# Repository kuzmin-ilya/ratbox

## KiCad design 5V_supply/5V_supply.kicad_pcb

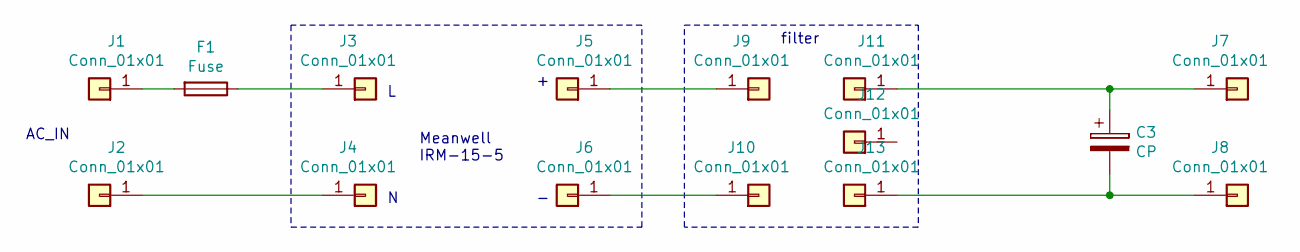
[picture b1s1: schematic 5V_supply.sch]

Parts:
C3: CP; CP_Radial_D13.0mm_P7.50mm
F1: Fuse; Fuseholder_Cylinder-5x20mm_Schurter_0031_8201_Horizontal_Op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
J1, J2, J7, J8: Conn_01x01; SolderWirePad_1x01_Drill2mm
J3, J4, J5, J6: Conn_01x01; SolderWirePad_1x01_Drill1.5mm
J9, J10, J11, J12, J13: Conn_01x01; SolderWirePad_1x01_Drill2.5mm

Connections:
unnamed: C3.1, J7.1, J11.1
unnamed: C3.2, J8.1, J13.1
unnamed: F1.1, J3.1
unnamed: F1.2, J1.1
unnamed: J2.1, J4.1
unnamed: J5.1, J9.1
unnamed: J6.1, J10.1

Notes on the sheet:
AC_IN
Meanwell IRM-15-5
filter

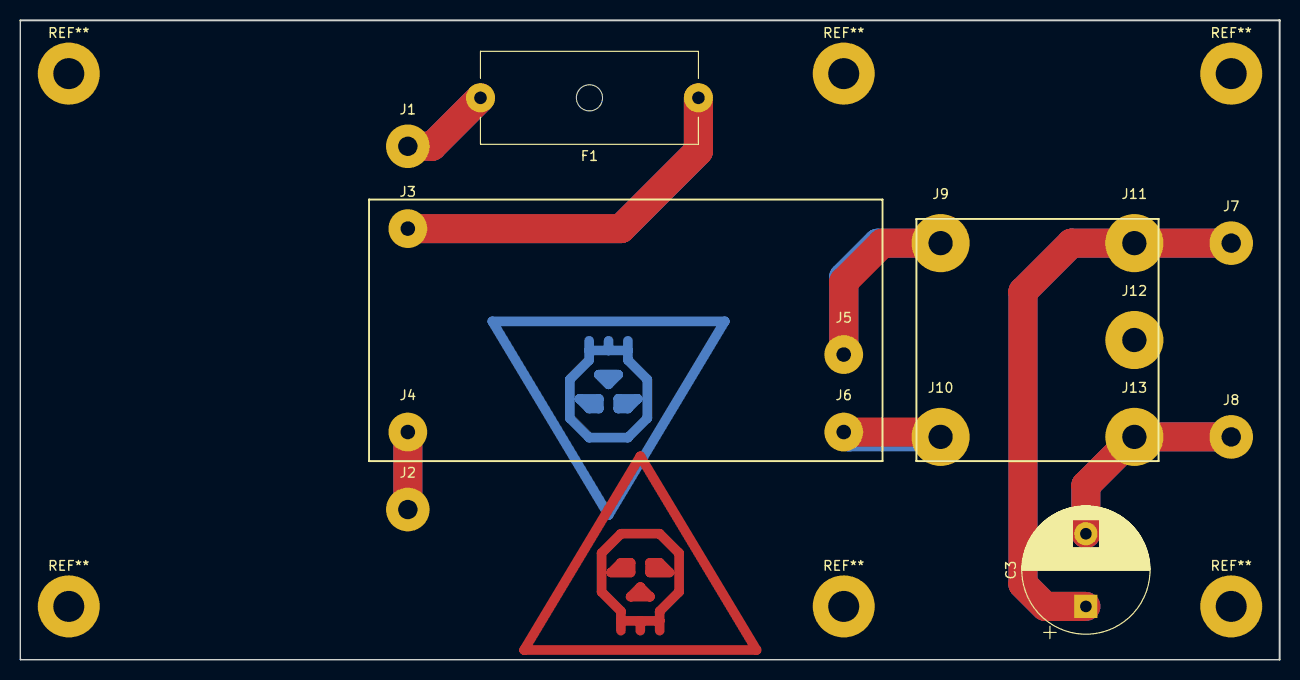
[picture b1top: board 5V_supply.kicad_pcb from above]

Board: 2 copper layers, 130.0 x 66.0 mm, 15 parts (0 on the bottom side), 7 nets.

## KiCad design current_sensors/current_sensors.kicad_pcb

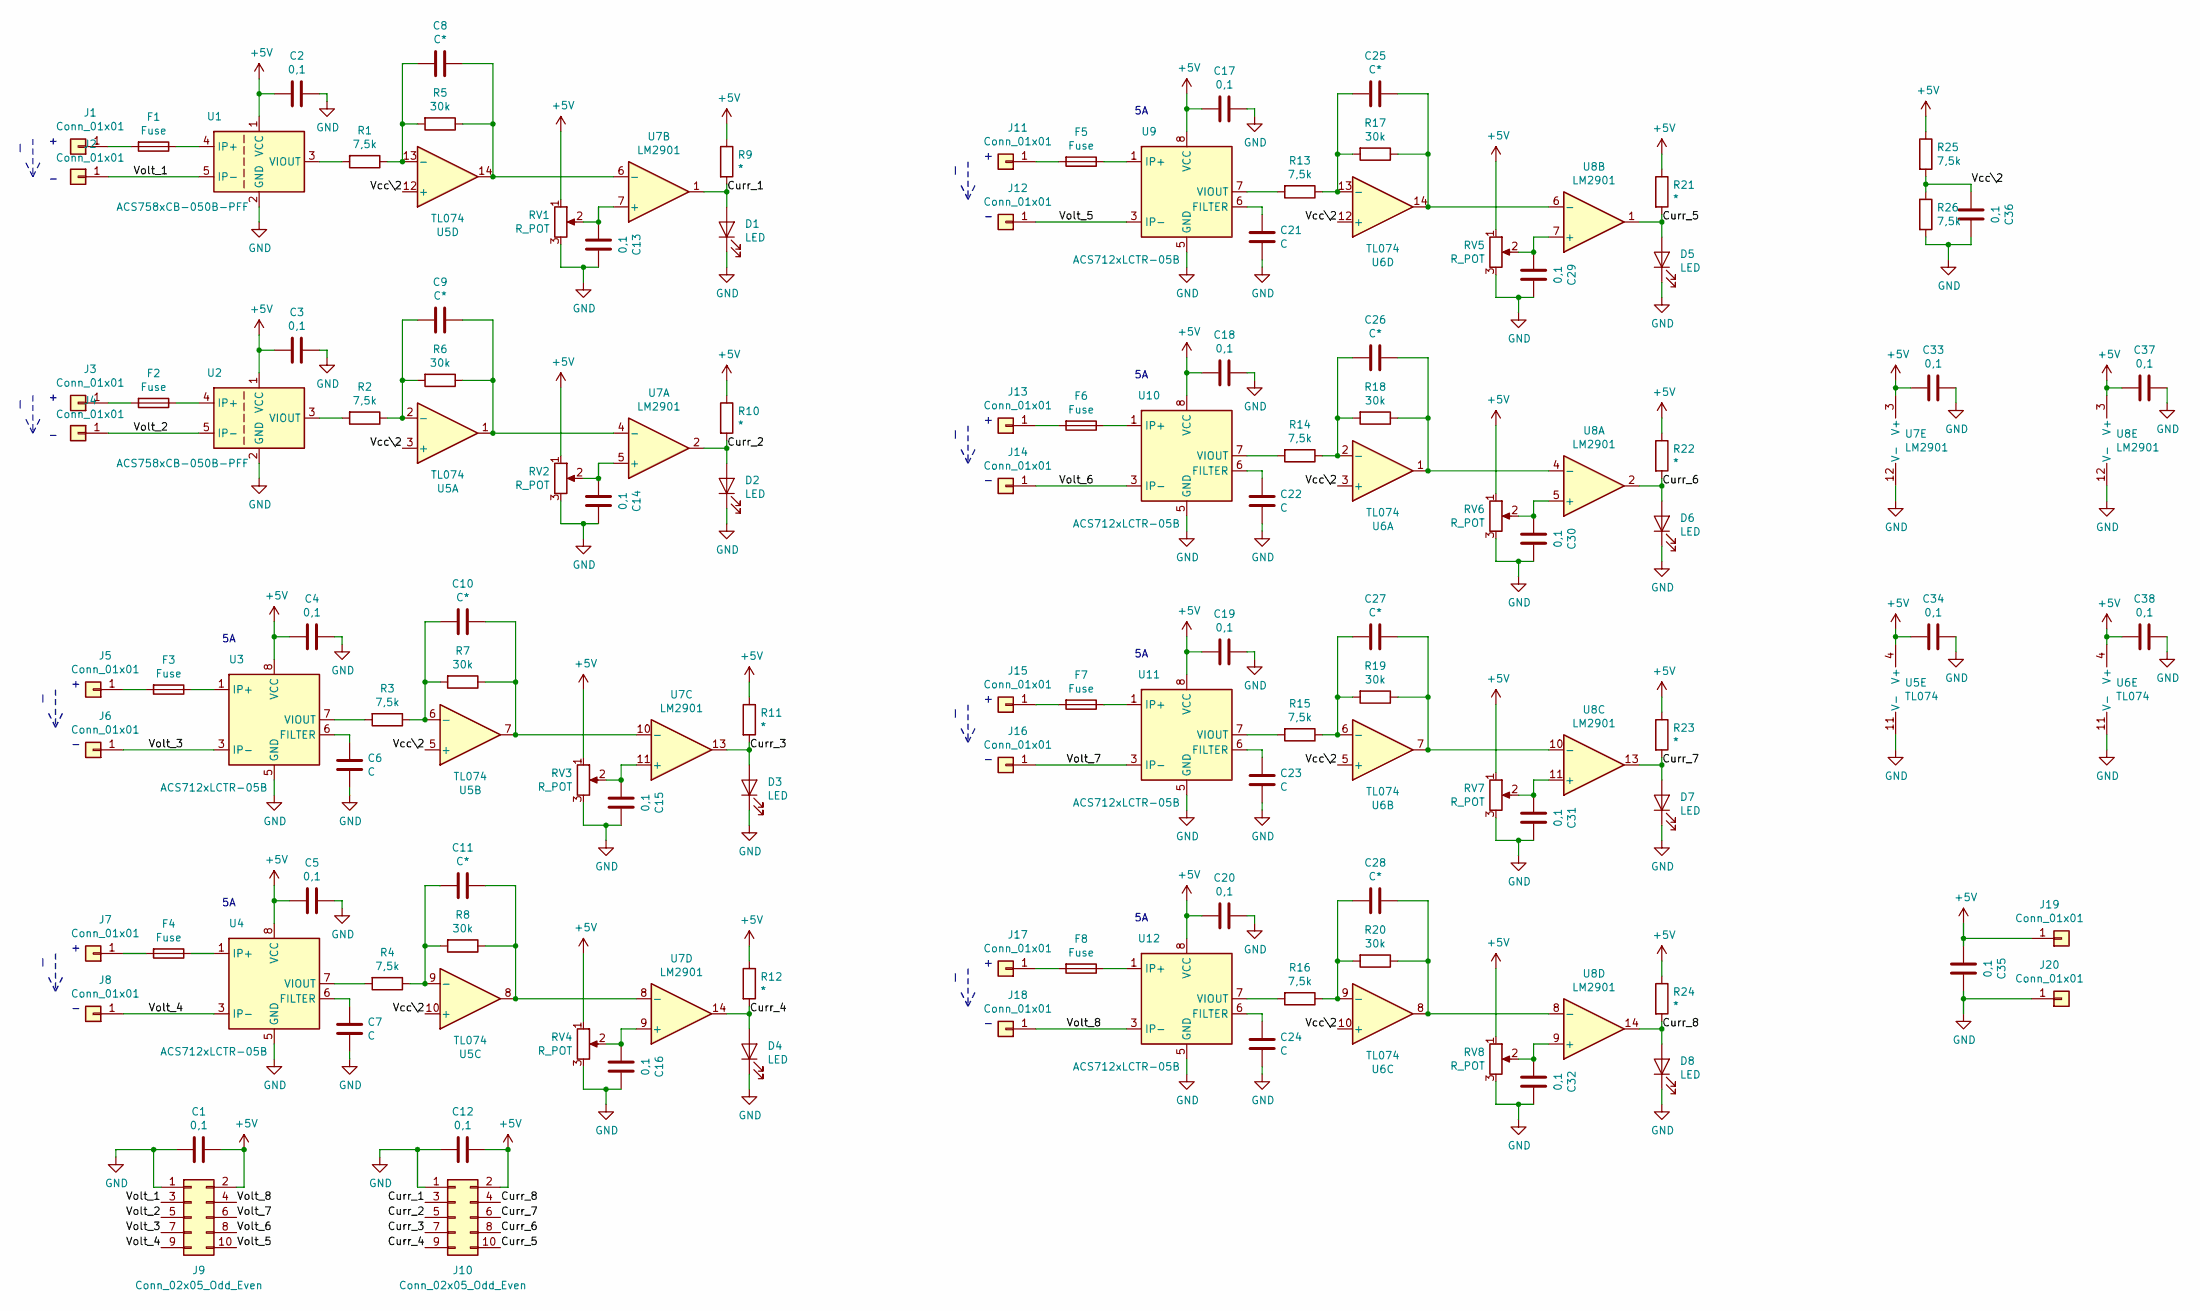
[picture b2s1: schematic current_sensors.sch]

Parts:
C1, C2, C3, C4, C5, C12, C13, C14, C15, C16, C17, C18, C19, C20, C29, C30, C31, C32, C33, C34, C35, C36, C37, C38: 0,1; C_0805_2012Metric_Pad1.15x1.40mm_HandSolder
C6, C7, C21, C22, C23, C24: C; C_0805_2012Metric_Pad1.15x1.40mm_HandSolder
C8, C9, C10, C11, C25, C26, C27, C28: C*; C_0805_2012Metric_Pad1.15x1.40mm_HandSolder
D1, D2, D3, D4, D5, D6, D7, D8: LED; LED_D5.0mm
F1, F2, F3, F4, F5, F6, F7, F8: Fuse; Fuseholder_Cylinder-5x20mm_Schurter_0031_8201_Horizontal_Op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
J1, J2, J3, J4, J5, J6, J7, J8, J11, J12, J13, J14, J15, J16, J17, J18, J19, J20: Conn_01x01; SolderWirePad_1x01_Drill2mm
J9, J10: Conn_02x05_Odd_Even; IDC-Header_2x05_P2.54mm_Vertical
R1, R2, R3, R4, R13, R14, R15, R16, R25, R26: 7,5k; R_0805_2012Metric_Pad1.15x1.40mm_HandSolder
R5, R6, R7, R8, R17, R18, R19, R20: 30k; R_0805_2012Metric_Pad1.15x1.40mm_HandSolder
R9, R10, R11, R12, R21, R22, R23, R24: *; R_0805_2012Metric_Pad1.15x1.40mm_HandSolder
RV1, RV2, RV3, RV4, RV5, RV6, RV7, RV8: R_POT; Potentiometer_Bourns_3296W_Vertical
U1, U2: ACS758xCB-050B-PFF; Allegro_CB_PFF
U3, U4, U9, U10, U11, U12: ACS712xLCTR-05B; SOIC-8_3.9x4.9mm_P1.27mm
U5, U6: TL074; SOIC-14_3.9x8.7mm_P1.27mm
U7, U8: LM2901; SOIC-14_3.9x8.7mm_P1.27mm

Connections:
+5V: C1.1, C2.2, C3.2, C4.2, C5.2, C12.1, C17.2, C18.2, C19.2, C20.2, C33.2, C34.2, C35.2, C37.2, C38.2, J9.2, J10.2, J19.1, R9.1, R10.1, R11.1, R12.1, R21.1, R22.1, R23.1, R24.1, R25.1, RV1.1, RV2.1, RV3.1, RV4.1, RV5.1, RV6.1, RV7.1, RV8.1, U1.1 (VCC), U2.1 (VCC), U3.8 (VCC), U4.8 (VCC), U5.4 (V+), U6.4 (V+), U7.3 (V+), U8.3 (V+), U9.8 (VCC), U10.8 (VCC), U11.8 (VCC), U12.8 (VCC)
/Curr_1: D1.2 (A), J10.3, R9.2, U7.1
/Curr_2: D2.2 (A), J10.5, R10.2, U7.2
/Curr_3: D3.2 (A), J10.7, R11.2, U7.13
/Curr_4: D4.2 (A), J10.9, R12.2, U7.14
/Curr_5: D5.2 (A), J10.10, R21.2, U8.1
/Curr_6: D6.2 (A), J10.8, R22.2, U8.2
/Curr_7: D7.2 (A), J10.6, R23.2, U8.13
/Curr_8: D8.2 (A), J10.4, R24.2, U8.14
/Vcc\2: C36.2, R25.2, R26.1, U5.3 (+), U5.5 (+), U5.10 (+), U5.12 (+), U6.3 (+), U6.5 (+), U6.10 (+), U6.12 (+)
/Volt_1: J2.1, J9.3, U1.5 (IP-)
/Volt_2: J4.1, J9.5, U2.5 (IP-)
/Volt_3: J6.1, J9.7, U3.3 (IP-), U3.4 (IP-)
/Volt_4: J8.1, J9.9, U4.3 (IP-), U4.4 (IP-)
/Volt_5: J9.10, J12.1, U9.3 (IP-), U9.4 (IP-)
/Volt_6: J9.8, J14.1, U10.3 (IP-), U10.4 (IP-)
/Volt_7: J9.6, J16.1, U11.3 (IP-), U11.4 (IP-)
/Volt_8: J9.4, J18.1, U12.3 (IP-), U12.4 (IP-)
GND: C1.2, C2.1, C3.1, C4.1, C5.1, C6.2, C7.2, C12.2, C13.1, C14.1, C15.1, C16.1, C17.1, C18.1, C19.1, C20.1, C21.2, C22.2, C23.2, C24.2, C29.1, C30.1, C31.1, C32.1, C33.1, C34.1, C35.1, C36.1, C37.1, C38.1, D1.1 (K), D2.1 (K), D3.1 (K), D4.1 (K), D5.1 (K), D6.1 (K), D7.1 (K), D8.1 (K), J9.1, J10.1, J20.1, R26.2, RV1.3, RV2.3, RV3.3, RV4.3, RV5.3, RV6.3, RV7.3, RV8.3, U1.2 (GND), U2.2 (GND), U3.5 (GND), U4.5 (GND), U5.11 (V-), U6.11 (V-), U7.12 (V-), U8.12 (V-), U9.5 (GND), U10.5 (GND), U11.5 (GND), U12.5 (GND)
unnamed: C6.1, U3.6 (FILTER)
unnamed: C7.1, U4.6 (FILTER)
unnamed: C8.1, R5.1, U5.14, U7.6 (-)
unnamed: C8.2, R1.1, R5.2, U5.13 (-)
unnamed: C9.1, R6.1, U5.1, U7.4 (-)
unnamed: C9.2, R2.1, R6.2, U5.2 (-)
unnamed: C10.1, R7.1, U5.7, U7.10 (-)
unnamed: C10.2, R3.1, R7.2, U5.6 (-)
unnamed: C11.1, R8.1, U5.8, U7.8 (-)
unnamed: C11.2, R4.1, R8.2, U5.9 (-)
unnamed: C13.2, RV1.2, U7.7 (+)
unnamed: C14.2, RV2.2, U7.5 (+)
unnamed: C15.2, RV3.2, U7.11 (+)
unnamed: C16.2, RV4.2, U7.9 (+)
unnamed: C21.1, U9.6 (FILTER)
unnamed: C22.1, U10.6 (FILTER)
unnamed: C23.1, U11.6 (FILTER)
unnamed: C24.1, U12.6 (FILTER)
unnamed: C25.1, R17.1, U6.14, U8.6 (-)
unnamed: C25.2, R13.1, R17.2, U6.13 (-)
unnamed: C26.1, R18.1, U6.1, U8.4 (-)
unnamed: C26.2, R14.1, R18.2, U6.2 (-)
unnamed: C27.1, R19.1, U6.7, U8.10 (-)
unnamed: C27.2, R15.1, R19.2, U6.6 (-)
unnamed: C28.1, R20.1, U6.8, U8.8 (-)
unnamed: C28.2, R16.1, R20.2, U6.9 (-)
unnamed: C29.2, RV5.2, U8.7 (+)
unnamed: C30.2, RV6.2, U8.5 (+)
unnamed: C31.2, RV7.2, U8.11 (+)
unnamed: C32.2, RV8.2, U8.9 (+)
unnamed: F1.1, U1.4 (IP+)
unnamed: F1.2, J1.1
unnamed: F2.1, U2.4 (IP+)
unnamed: F2.2, J3.1
unnamed: F3.1, U3.1 (IP+), U3.2 (IP+)
unnamed: F3.2, J5.1
unnamed: F4.1, U4.1 (IP+), U4.2 (IP+)
unnamed: F4.2, J7.1
unnamed: F5.1, U9.1 (IP+), U9.2 (IP+)
unnamed: F5.2, J11.1
unnamed: F6.1, U10.1 (IP+), U10.2 (IP+)
unnamed: F6.2, J13.1
unnamed: F7.1, U11.1 (IP+), U11.2 (IP+)
unnamed: F7.2, J15.1
unnamed: F8.1, U12.1 (IP+), U12.2 (IP+)
unnamed: F8.2, J17.1
unnamed: R1.2, U1.3 (VIOUT)
unnamed: R2.2, U2.3 (VIOUT)
unnamed: R3.2, U3.7 (VIOUT)
unnamed: R4.2, U4.7 (VIOUT)
unnamed: R13.2, U9.7 (VIOUT)
unnamed: R14.2, U10.7 (VIOUT)
unnamed: R15.2, U11.7 (VIOUT)
unnamed: R16.2, U12.7 (VIOUT)

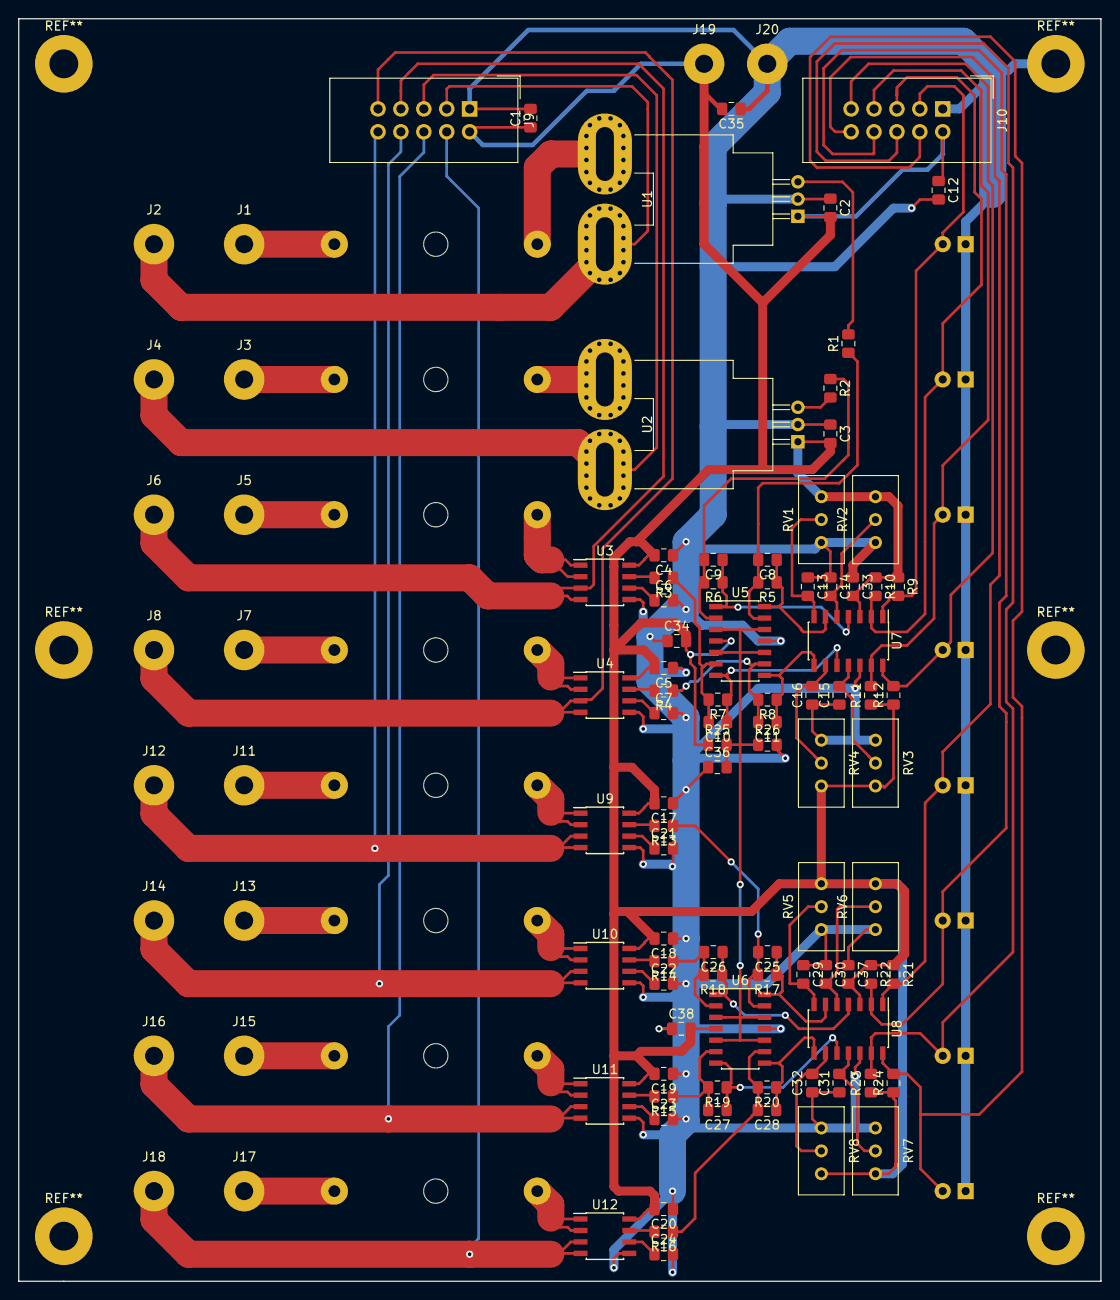
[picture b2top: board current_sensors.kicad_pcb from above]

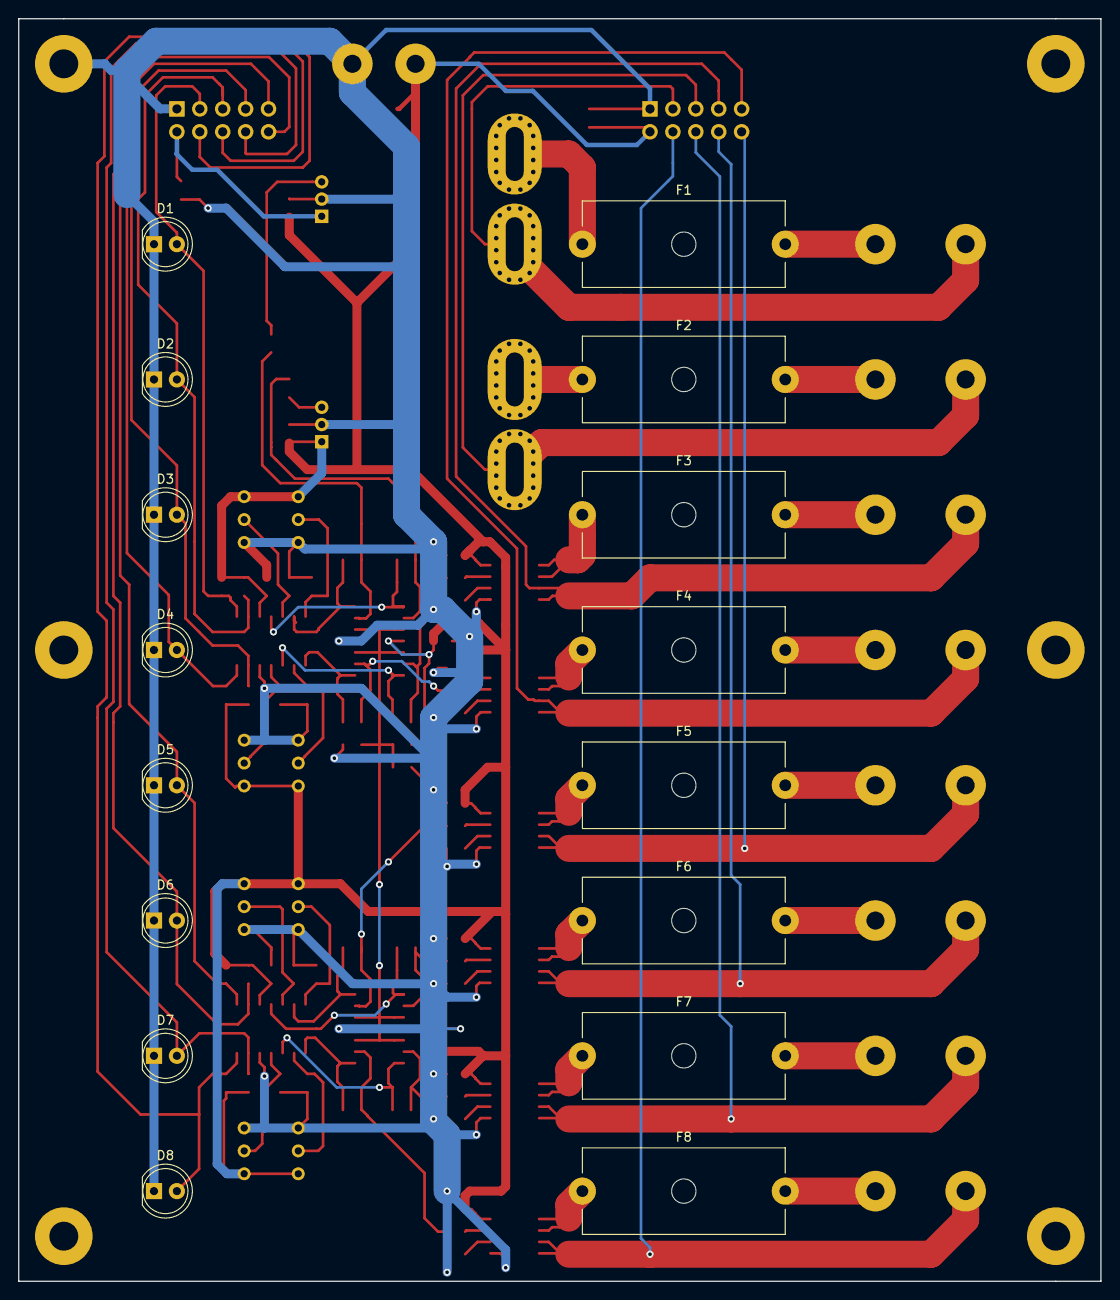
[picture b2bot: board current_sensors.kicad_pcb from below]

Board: 2 copper layers, 120.0 x 140.0 mm, 120 parts (16 on the bottom side), 73 nets.

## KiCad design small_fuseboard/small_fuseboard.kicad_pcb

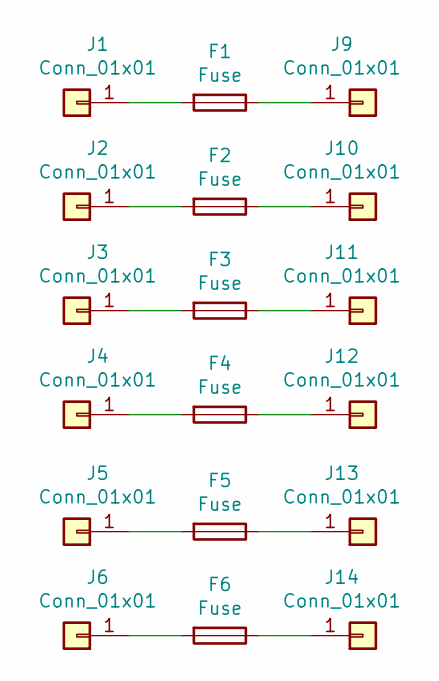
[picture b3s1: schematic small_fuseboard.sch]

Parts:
F1, F2, F3, F4, F5, F6: Fuse; Fuseholder_Cylinder-5x20mm_Schurter_0031_8201_Horizontal_Op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
J1, J2, J3, J4, J5, J6, J9, J10, J11, J12, J13, J14: Conn_01x01; MountingHole_3.2mm_M3_Pad

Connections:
unnamed: F1.1, J9.1
unnamed: F1.2, J1.1
unnamed: F2.1, J10.1
unnamed: F2.2, J2.1
unnamed: F3.1, J11.1
unnamed: F3.2, J3.1
unnamed: F4.1, J12.1
unnamed: F4.2, J4.1
unnamed: F5.1, J13.1
unnamed: F5.2, J5.1
unnamed 10: F6.1, J14.1; also elsewhere on the board
unnamed 11: F6.2, J6.1; also elsewhere on the board

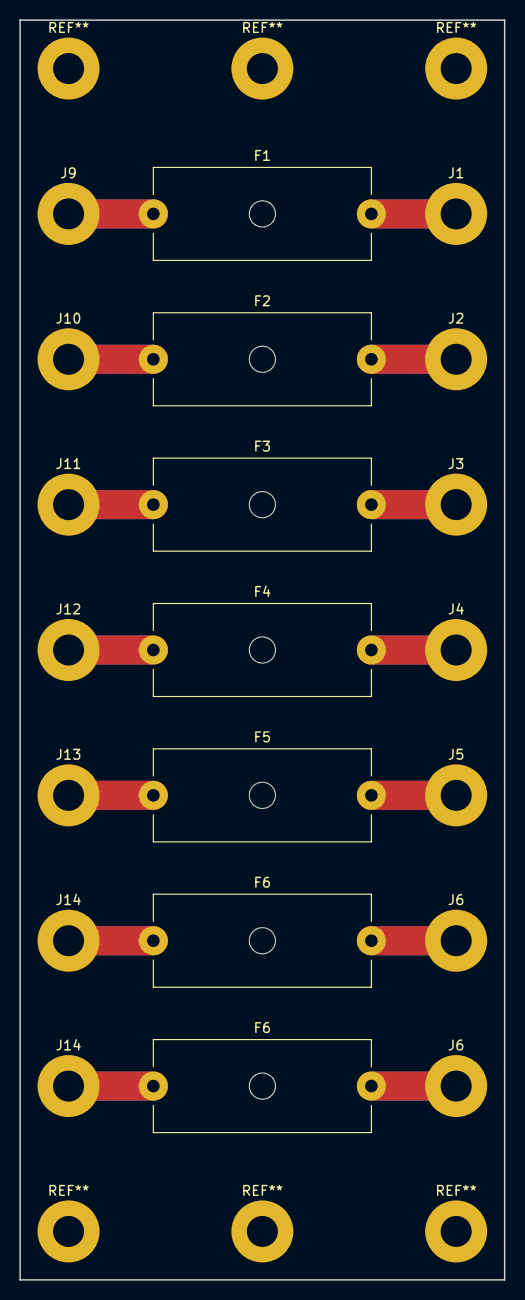
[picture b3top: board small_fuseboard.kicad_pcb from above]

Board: 2 copper layers, 50.0 x 130.0 mm, 21 parts (0 on the bottom side), 12 nets.

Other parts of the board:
F6#2: Fuse; Fuseholder_Cylinder-5x20mm_Schurter_0031_8201_Horizontal_Op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
J6#2, J14#2: Conn_01x01; MountingHole_3.2mm_M3_Pad

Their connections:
unnamed 10: F6#2.1, J14#2.1; also elsewhere on the board
unnamed 11: F6#2.2, J6#2.1; also elsewhere on the board

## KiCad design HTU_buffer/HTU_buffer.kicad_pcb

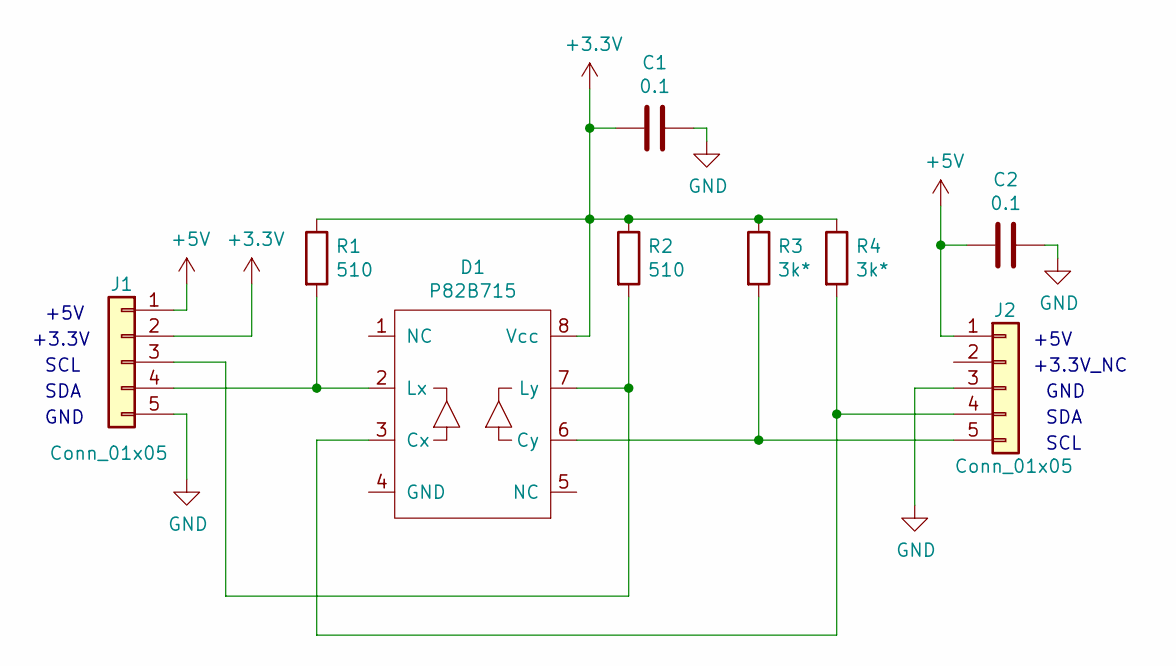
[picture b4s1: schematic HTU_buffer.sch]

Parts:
C1, C2: 0.1; C_0805_2012Metric_Pad1.15x1.40mm_HandSolder
D1: P82B715; SOIC-8_3.9x4.9mm_P1.27mm
J1: Conn_01x05; PinHeader_1x05_P2.54mm_Horizontal
J2: Conn_01x05; PinSocket_1x05_P2.54mm_Vertical
R1, R2: 510; R_0805_2012Metric_Pad1.15x1.40mm_HandSolder
R3, R4: 3k*; R_0805_2012Metric_Pad1.15x1.40mm_HandSolder

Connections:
+3V3: C1.1, D1.8 (Vcc), J1.2, R1.1, R2.1, R3.1, R4.1
+5V: C2.2, J1.1, J2.1
GND: C1.2, C2.1, J1.5, J2.3
unnamed: D1.2 (Lx), J1.4, R1.2
unnamed: D1.3 (Cx), J2.4, R4.2
unnamed: D1.6 (Cy), J2.5, R3.2
unnamed: D1.7 (Ly), J1.3, R2.2

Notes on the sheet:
+5V
+3.3V_NC
GND
SDA
SCL
+3.3V

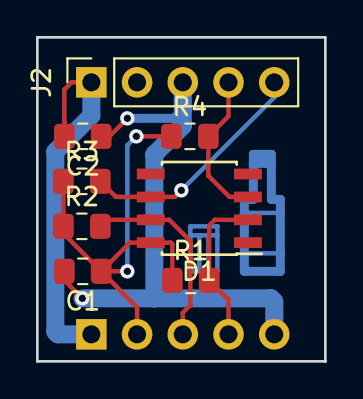
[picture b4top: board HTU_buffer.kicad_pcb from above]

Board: 2 copper layers, 16.0 x 18.0 mm, 9 parts (1 on the bottom side), 7 nets.

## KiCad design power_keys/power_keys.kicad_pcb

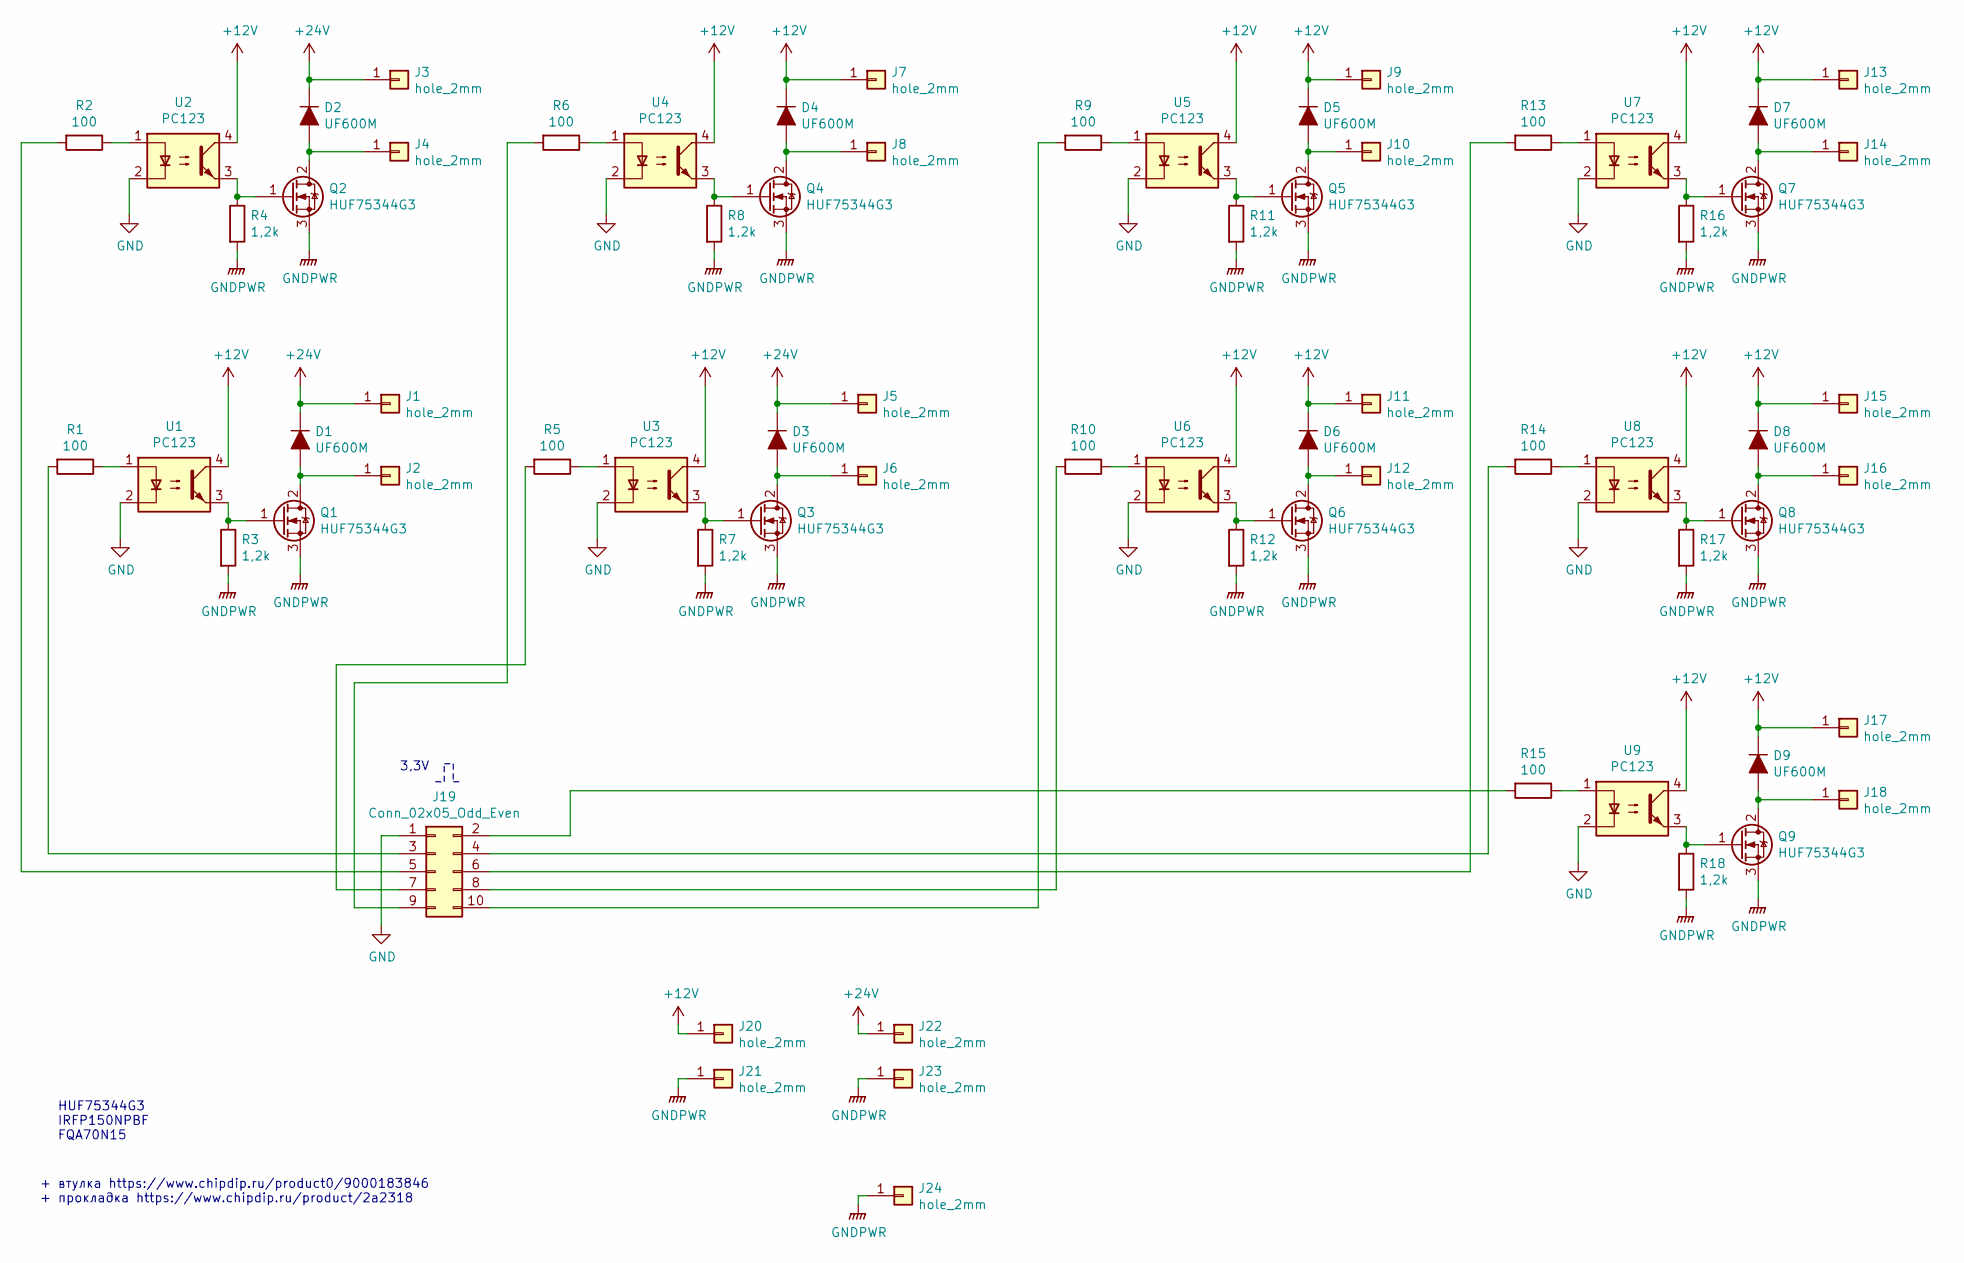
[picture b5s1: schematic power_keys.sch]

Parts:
D1, D2, D3, D4, D5, D6, D7, D8, D9: UF600M; D_P600_R-6_P20.00mm_Horizontal
J1, J2, J3, J4, J5, J6, J7, J8, J9, J10, J11, J12, J13, J14, J15, J16, J17, J18, J20, J21, J22, J23, J24: hole_2mm; SolderWirePad_1x01_Drill2mm
J19: Conn_02x05_Odd_Even; IDC-Header_2x05_P2.54mm_Vertical
Q1, Q2, Q3, Q4, Q5, Q6, Q7, Q8, Q9: HUF75344G3; TO-247-3_Horizontal_TabDown
R1, R2, R5, R6, R9, R10, R13, R14, R15: 100; R_Axial_DIN0411_L9.9mm_D3.6mm_P12.70mm_Horizontal
R3, R4, R7, R8, R11, R12, R16, R17, R18: 1,2k; R_Axial_DIN0411_L9.9mm_D3.6mm_P12.70mm_Horizontal
U1, U2, U3, U4, U5, U6, U7, U8, U9: PC123; DIP-4_W7.62mm_LongPads

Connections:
+12V: D4.1 (K), D5.1 (K), D6.1 (K), D7.1 (K), D8.1 (K), D9.1 (K), J7.1, J9.1, J11.1, J13.1, J15.1, J17.1, J20.1, U1.4, U2.4, U3.4, U4.4, U5.4, U6.4, U7.4, U8.4, U9.4
+24V: D1.1 (K), D2.1 (K), D3.1 (K), J1.1, J3.1, J5.1, J22.1
GND: J19.1, U1.2, U2.2, U3.2, U4.2, U5.2, U6.2, U7.2, U8.2, U9.2
GNDPWR: J21.1, J23.1, J24.1, Q1.3 (S), Q2.3 (S), Q3.3 (S), Q4.3 (S), Q5.3 (S), Q6.3 (S), Q7.3 (S), Q8.3 (S), Q9.3 (S), R3.2, R4.2, R7.2, R8.2, R11.2, R12.2, R16.2, R17.2, R18.2
unnamed: D1.2 (A), J2.1, Q1.2 (D)
unnamed: D2.2 (A), J4.1, Q2.2 (D)
unnamed: D3.2 (A), J6.1, Q3.2 (D)
unnamed: D4.2 (A), J8.1, Q4.2 (D)
unnamed: D5.2 (A), J10.1, Q5.2 (D)
unnamed: D6.2 (A), J12.1, Q6.2 (D)
unnamed: D7.2 (A), J14.1, Q7.2 (D)
unnamed: D8.2 (A), J16.1, Q8.2 (D)
unnamed: D9.2 (A), J18.1, Q9.2 (D)
unnamed: J19.2, R15.2
unnamed: J19.3, R1.2
unnamed: J19.4, R14.2
unnamed: J19.5, R2.2
unnamed: J19.6, R13.2
unnamed: J19.7, R5.2
unnamed: J19.8, R10.2
unnamed: J19.9, R6.2
unnamed: J19.10, R9.2
unnamed: Q1.1 (G), R3.1, U1.3
unnamed: Q2.1 (G), R4.1, U2.3
unnamed: Q3.1 (G), R7.1, U3.3
unnamed: Q4.1 (G), R8.1, U4.3
unnamed: Q5.1 (G), R11.1, U5.3
unnamed: Q6.1 (G), R12.1, U6.3
unnamed: Q7.1 (G), R16.1, U7.3
unnamed: Q8.1 (G), R17.1, U8.3
unnamed: Q9.1 (G), R18.1, U9.3
unnamed: R1.1, U1.1
unnamed: R2.1, U2.1
unnamed: R5.1, U3.1
unnamed: R6.1, U4.1
unnamed: R9.1, U5.1
unnamed: R10.1, U6.1
unnamed: R13.1, U7.1
unnamed: R14.1, U8.1
unnamed: R15.1, U9.1

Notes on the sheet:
+ втулка https://www.chipdip.ru/product0/9000183846 + прокладка https://www.chipdip.ru/product/2a2318
HUF75344G3 IRFP150NPBF FQA70N15
3,3V

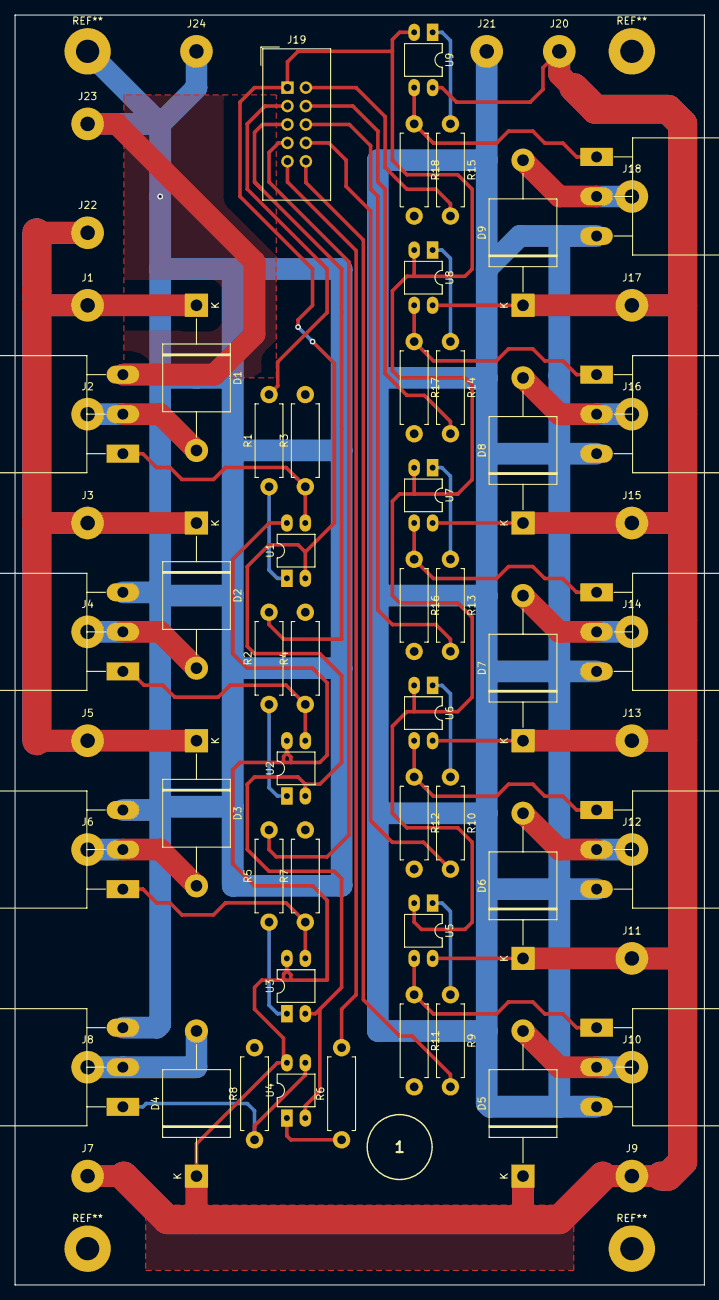
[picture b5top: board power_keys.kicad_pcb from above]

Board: 2 copper layers, 95.0 x 175.0 mm, 69 parts (0 on the bottom side), 40 nets.

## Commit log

2019-11-02 initial commit, power board added
2019-11-02 trash rmved, power board added
2019-11-02 mainboard added
2019-11-10 mainboard: work in progress
2019-11-13 current sensors: work in progress
2019-11-13 fixup! mainboard: work in progress
2019-11-18 mainboard finished
2019-11-24 HTU bufer added
2019-11-24 5V_supply added
2019-11-24 small cutable fuseboard added
2019-11-25 current-sensors: work in progress
2019-11-27 current-sensors finished
2019-11-28 power supply finished
